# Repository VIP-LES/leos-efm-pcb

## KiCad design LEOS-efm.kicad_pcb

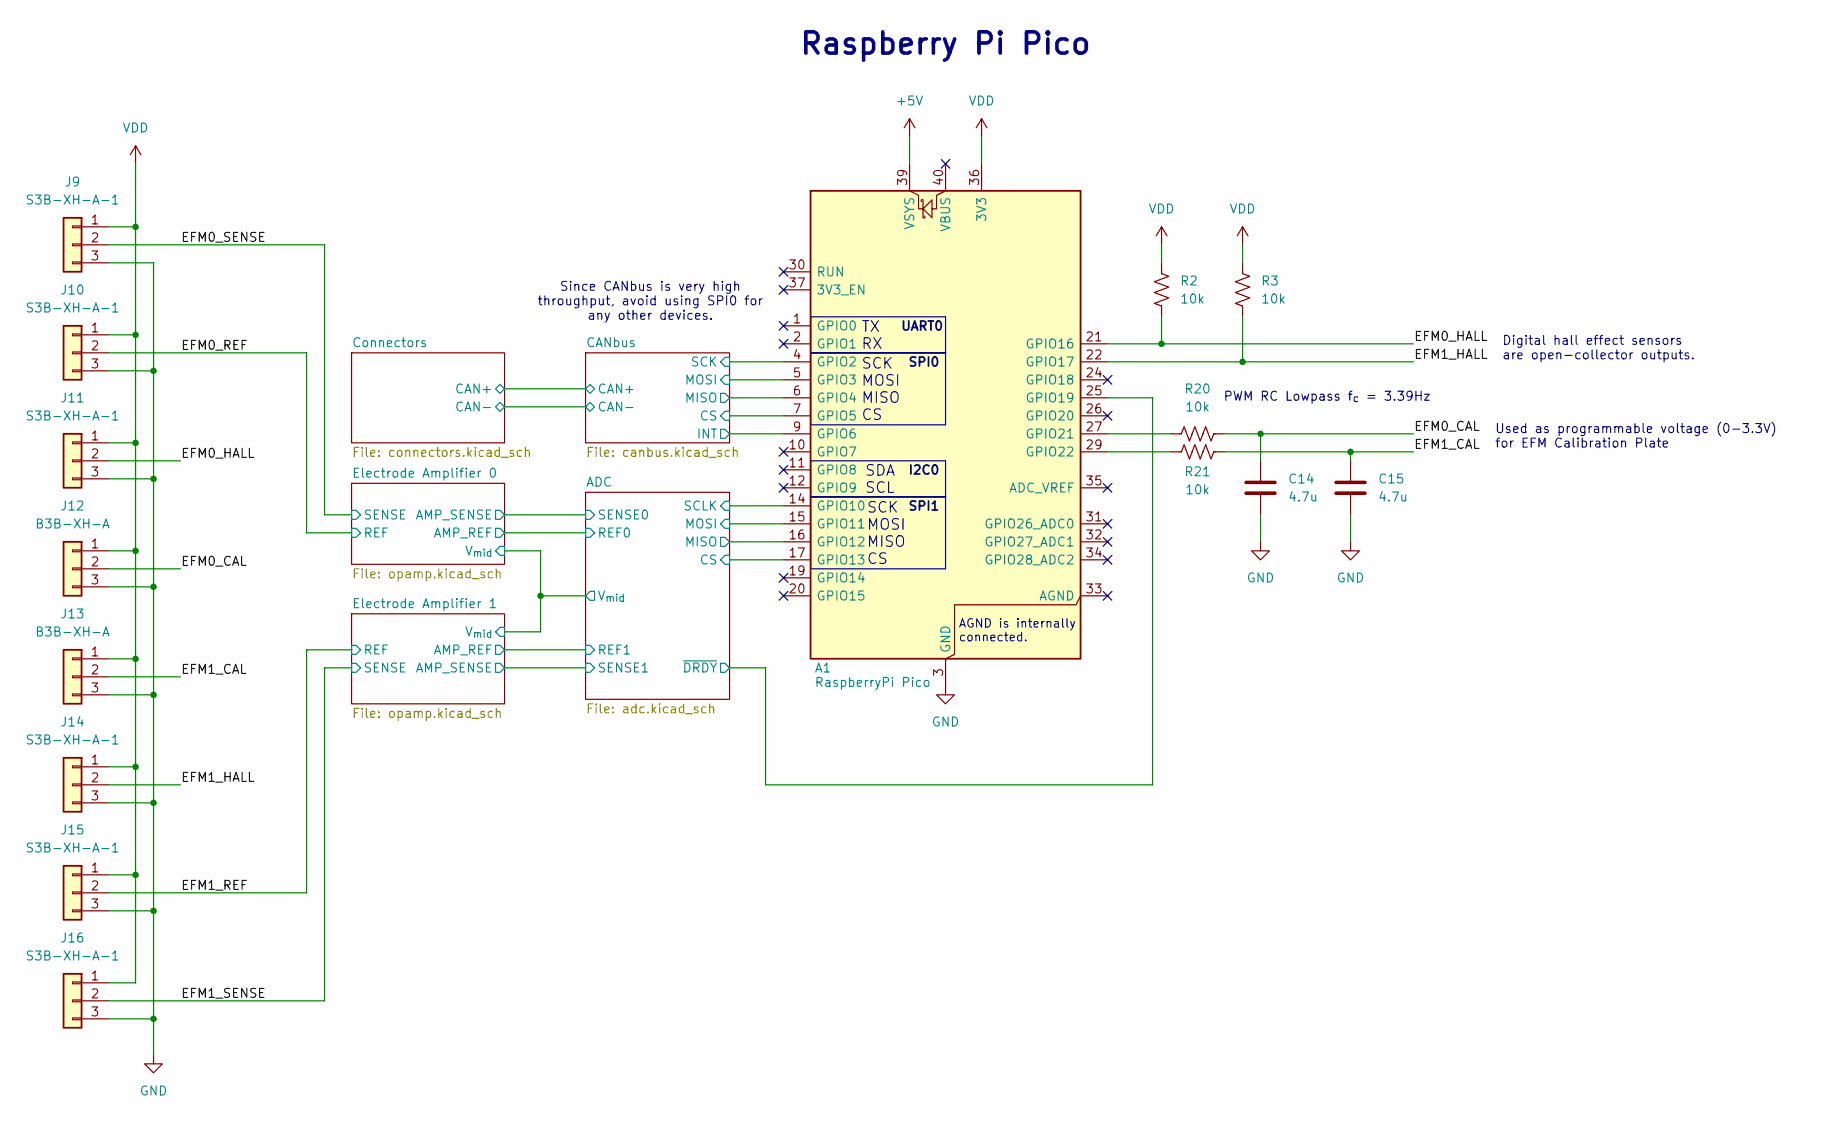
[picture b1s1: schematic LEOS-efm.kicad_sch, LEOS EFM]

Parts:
A1: RaspberryPi Pico; RaspberryPi_Pico_Common_Unspecified; MPN PIM724; Digikey 1778-PIM724-ND
C14, C15: 4.7u; C_1206_3216Metric; MPN CL31B475KBHNFNE; Digikey 1276-3179-1-ND
J9, J10, J11, J14, J15, J16: S3B-XH-A-1; JST_XH_S3B-XH-A-1_1x03_P2.50mm_Horizontal; MPN S3B-XH-A-1; Digikey 455-S3B-XH-A-1-ND
J12, J13: B3B-XH-A; JST_XH_B3B-XH-A_1x03_P2.50mm_Vertical; MPN B3B-XH-A; Digikey 455-2248-ND
R2, R3, R20, R21: 10k; R_1206_3216Metric

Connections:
+5V: A1.39 (VSYS); also elsewhere on the board
/ADC/CS: A1.17 (GPIO13); also elsewhere on the board
/ADC/MISO: A1.16 (GPIO12); also elsewhere on the board
/ADC/MOSI: A1.15 (GPIO11); also elsewhere on the board
/ADC/SCLK: A1.14 (GPIO10); also elsewhere on the board
/ADC/~DRDY: A1.25 (GPIO19); also elsewhere on the board
/CANbus/CS: A1.7 (GPIO5); also elsewhere on the board
/CANbus/INT: A1.9 (GPIO6); also elsewhere on the board
/CANbus/MISO: A1.6 (GPIO4); also elsewhere on the board
/CANbus/MOSI: A1.5 (GPIO3); also elsewhere on the board
/CANbus/SCK: A1.4 (GPIO2); also elsewhere on the board
/EFM0_CAL: C14.1, J12.2, R20.2
/EFM0_HALL: A1.21 (GPIO16), J11.2, R2.2
/EFM0_REF: J10.2; also elsewhere on the board
/EFM0_SENSE: J9.2; also elsewhere on the board
/EFM1_CAL: C15.1, J13.2, R21.2
/EFM1_HALL: A1.22 (GPIO17), J14.2, R3.2
/EFM1_REF: J15.2; also elsewhere on the board
/EFM1_SENSE: J16.2; also elsewhere on the board
GND: A1.3 (GND), A1.8 (GND), A1.13 (GND), A1.18 (GND), A1.23 (GND), A1.28 (GND), A1.38 (GND), C14.2, C15.2, J9.3, J10.3, J11.3, J12.3, J13.3, J14.3, J15.3, J16.3; also elsewhere on the board
unnamed: A1.27 (GPIO21), R20.1
unnamed: A1.29 (GPIO22), R21.1
VDD: A1.36 (3V3), J9.1, J10.1, J11.1, J12.1, J13.1, J14.1, J15.1, J16.1, R2.1, R3.1; also elsewhere on the board

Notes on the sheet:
PWM RC Lowpass f_{c} = 3.39Hz
SPI1
Raspberry Pi Pico
SCK MOSI MISO CS
Since CANbus is very high throughput, avoid using SPI0 for any other devices.
SPI0
SDA SCL
TX RX
UART0
Digital hall effect sensors are open-collector outputs.
I2C0
AGND is internally connected.
Used as programmable voltage (0-3.3V) for EFM Calibration Plate

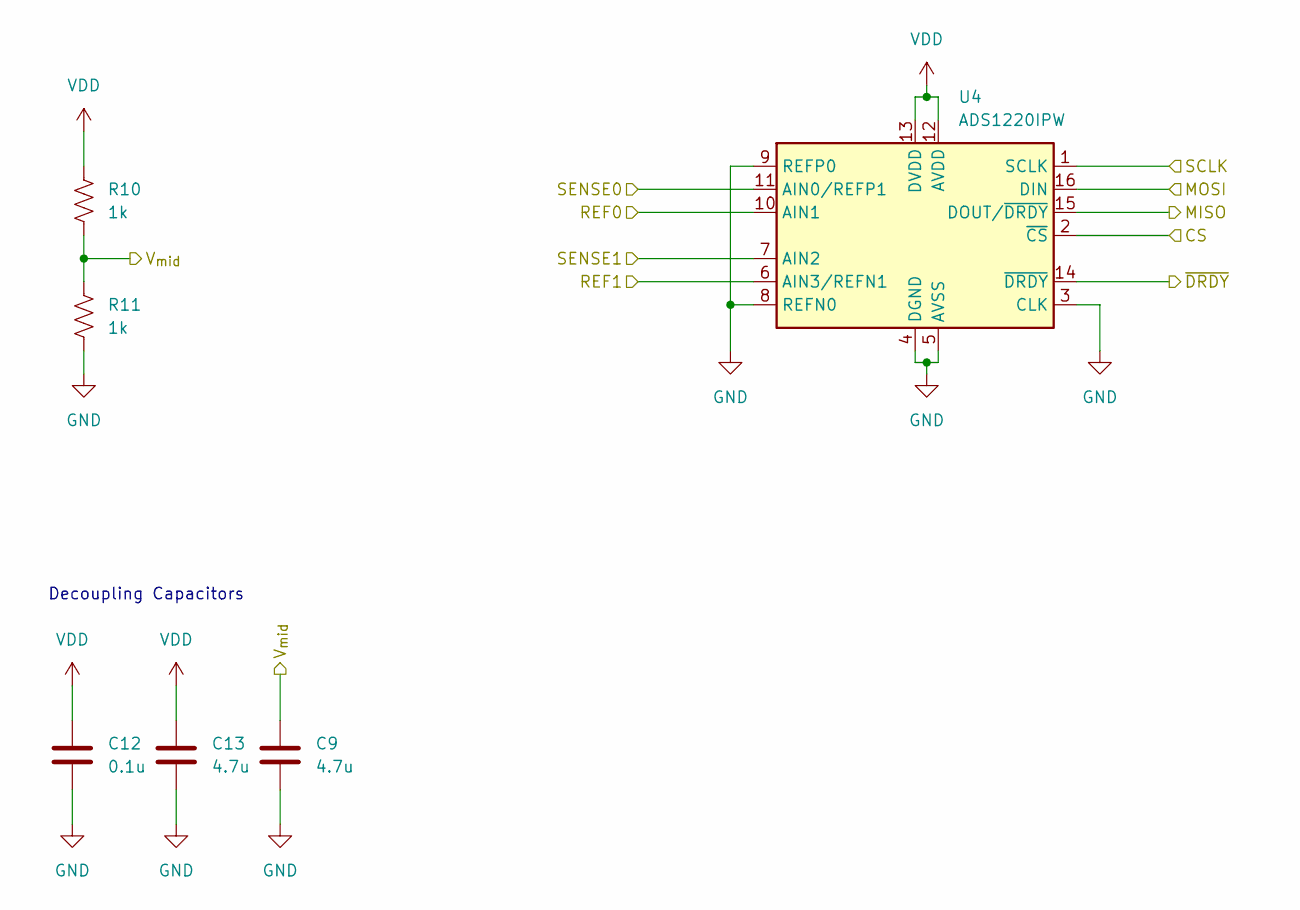
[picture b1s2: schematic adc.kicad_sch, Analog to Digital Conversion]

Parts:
C9, C13: 4.7u; C_1206_3216Metric; MPN CL31B475KBHNFNE; Digikey 1276-3179-1-ND
C12: 0.1u; C_0805_2012Metric; MPN CL21B104KBCNNNC; Digikey 1276-1003-1-ND
R10, R11: 1k; R_1206_3216Metric
U4: ADS1220IPW; TSSOP-16_4.4x5mm_P0.65mm; MPN ADS1220IPWR; Digikey 296-39851-1-ND

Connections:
/ADC/CS: U4.2 (~CS); also elsewhere on the board
/ADC/MISO: U4.15 (DOUT/~DRDY); also elsewhere on the board
/ADC/MOSI: U4.16 (DIN); also elsewhere on the board
/ADC/REF0: U4.10 (AIN1); also elsewhere on the board
/ADC/REF1: U4.6 (AIN3/REFN1); also elsewhere on the board
/ADC/SCLK: U4.1 (SCLK); also elsewhere on the board
/ADC/SENSE0: U4.11 (AIN0/REFP1); also elsewhere on the board
/ADC/SENSE1: U4.7 (AIN2); also elsewhere on the board
/ADC/V_{mid}: C9.1, R10.2, R11.1; also elsewhere on the board
/ADC/~DRDY: U4.14 (~DRDY); also elsewhere on the board
GND: C9.2, C12.2, C13.2, R11.2, U4.3 (CLK), U4.4 (DGND), U4.5 (AVSS), U4.8 (REFN0), U4.9 (REFP0); also elsewhere on the board
VDD: C12.1, C13.1, R10.1, U4.12 (AVDD), U4.13 (DVDD); also elsewhere on the board

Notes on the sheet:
Decoupling Capacitors

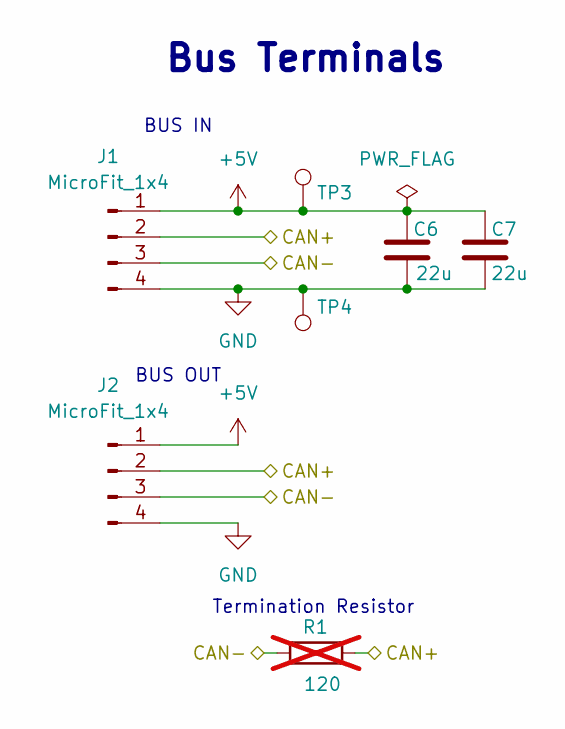
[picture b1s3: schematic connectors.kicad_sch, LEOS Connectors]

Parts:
C6, C7: 22u; C_1206_3216Metric; MPN CL31B226MPHNNNE; Digikey 1276-3148-1-ND
J1, J2: MicroFit_1x4; Molex_MicroFit3.0_43650-0410_1x04_Horizontal; MPN 0436500409; Digikey WM1882CT-ND
R1: 120; R_Axial_DIN0207_L6.3mm_D2.5mm_P7.62mm_Horizontal; MPN CF14JT120R; Digikey CF14JT120RCT-ND; not fitted
TP3: 5V Test Point; TestPoint_Loop_D2.60mm_Drill0.9mm_Beaded; MPN 5000; Digikey 36-5000-ND
TP4: GND Test Point; TestPoint_Loop_D2.60mm_Drill0.9mm_Beaded; MPN 5001; Digikey 36-5001-ND

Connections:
+5V: C6.1, C7.1, J1.1, J2.1, TP3.1 (1_1); also elsewhere on the board
/CANbus/CAN+: J1.2, J2.2, R1.2; also elsewhere on the board
/CANbus/CAN-: J1.3, J2.3, R1.1; also elsewhere on the board
GND: C6.2, C7.2, J1.4, J2.4, TP4.1 (1_1); also elsewhere on the board

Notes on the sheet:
BUS OUT
Bus Terminals
BUS IN
Termination Resistor

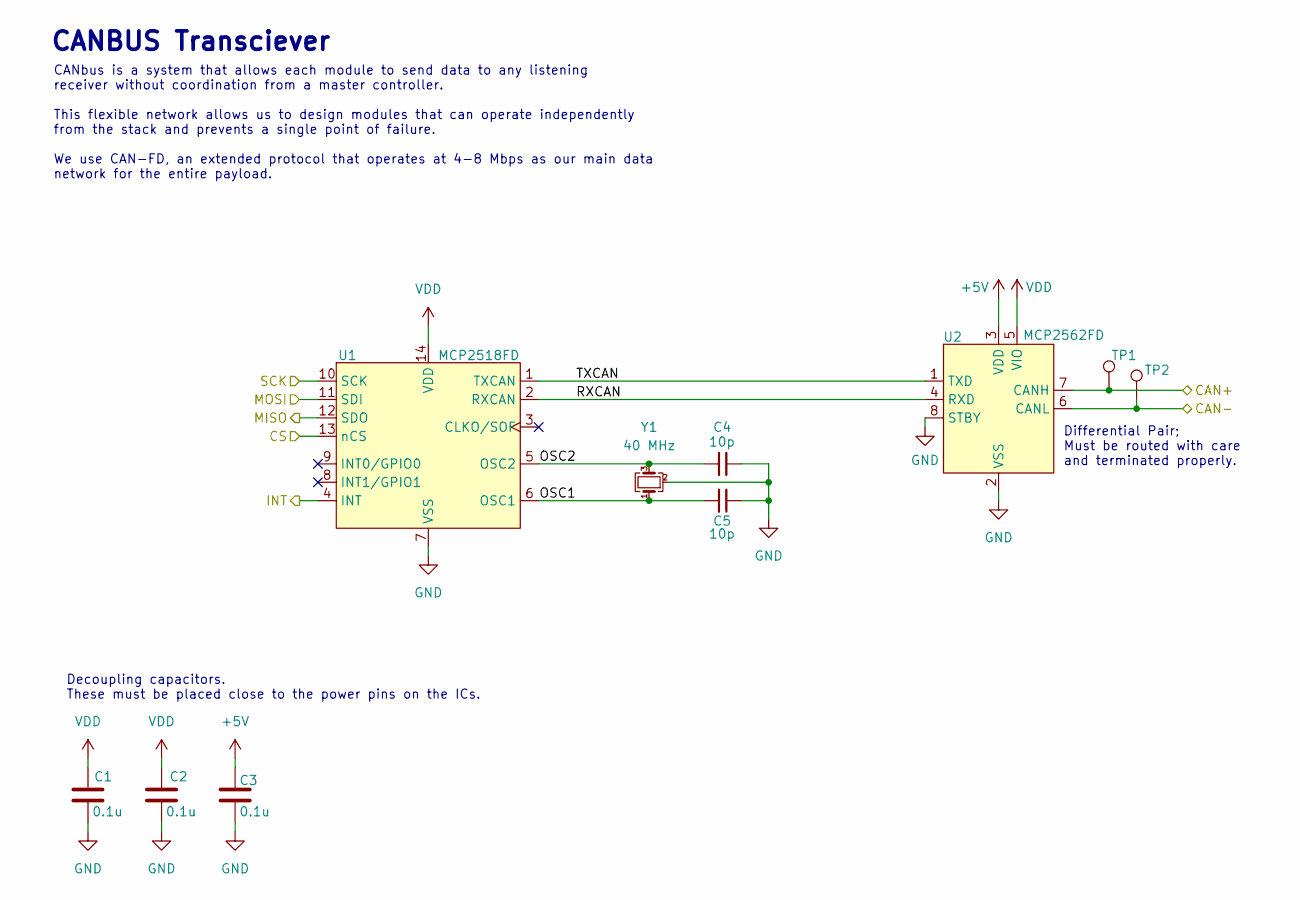
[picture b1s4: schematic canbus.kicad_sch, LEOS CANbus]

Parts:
C1, C2, C3: 0.1u; C_0805_2012Metric; MPN CL21B104KBCNNNC; Digikey 1276-1003-1-ND
C4, C5: 10p; C_0805_2012Metric; MPN CL21C100CBANNNC; Digikey 1276-2561-1-ND
TP1: CAN-H Test Point; TestPoint_Loop_D2.60mm_Drill0.9mm_Beaded; MPN 5004; Digikey 36-5004-ND
TP2: CAN-L Test Point; TestPoint_Loop_D2.60mm_Drill0.9mm_Beaded; MPN 5116; Digikey 36-5116-ND
U1: MCP2518FD; SOIC-14_3.9x8.7mm_P1.27mm; MPN MCP2518FDT-E/SL; LCSC C626758
U2: MCP2562FD; SOIC-8_3.9x4.9mm_P1.27mm; MPN MCP2562FDT-H/SN; LCSC C511335
Y1: 40 MHz; Crystal_SMD_2016-4Pin_2.0x1.6mm; MPN ECS-400-10-37B2-CKY-TR; Digikey 50-ECS-400-10-37B2-CKY-TRCT-ND

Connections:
+5V: C3.1, U2.3 (VDD); also elsewhere on the board
/CANbus/CAN+: TP1.1 (1_1), U2.7 (CANH); also elsewhere on the board
/CANbus/CAN-: TP2.1 (1_1), U2.6 (CANL); also elsewhere on the board
/CANbus/CS: U1.13 (nCS); also elsewhere on the board
/CANbus/INT: U1.4 (INT); also elsewhere on the board
/CANbus/MISO: U1.12 (SDO); also elsewhere on the board
/CANbus/MOSI: U1.11 (SDI); also elsewhere on the board
/CANbus/OSC1: C5.2, U1.6 (OSC1), Y1.1
/CANbus/OSC2: C4.2, U1.5 (OSC2), Y1.3
/CANbus/RXCAN: U1.2 (RXCAN), U2.4 (RXD)
/CANbus/SCK: U1.10 (SCK); also elsewhere on the board
/CANbus/TXCAN: U1.1 (TXCAN), U2.1 (TXD)
GND: C1.2, C2.2, C3.2, C4.1, C5.1, U1.7 (VSS), U2.2 (VSS), U2.8 (STBY), Y1.2 (G), Y1.4 (G); also elsewhere on the board
VDD: C1.1, C2.1, U1.14 (VDD), U2.5 (VIO); also elsewhere on the board

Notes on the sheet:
Differential Pair; Must be routed with care and terminated properly.
CANBUS Transciever
CANbus is a system that allows each module to send data to any listening receiver without coordination from a master controller. This flexible network allows us to design modules that can operate independently from the stack and prevents a single point of failure. We use CAN-FD, an extended protoco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
Decoupling capacitors. These must be placed close to the power pins on the ICs.

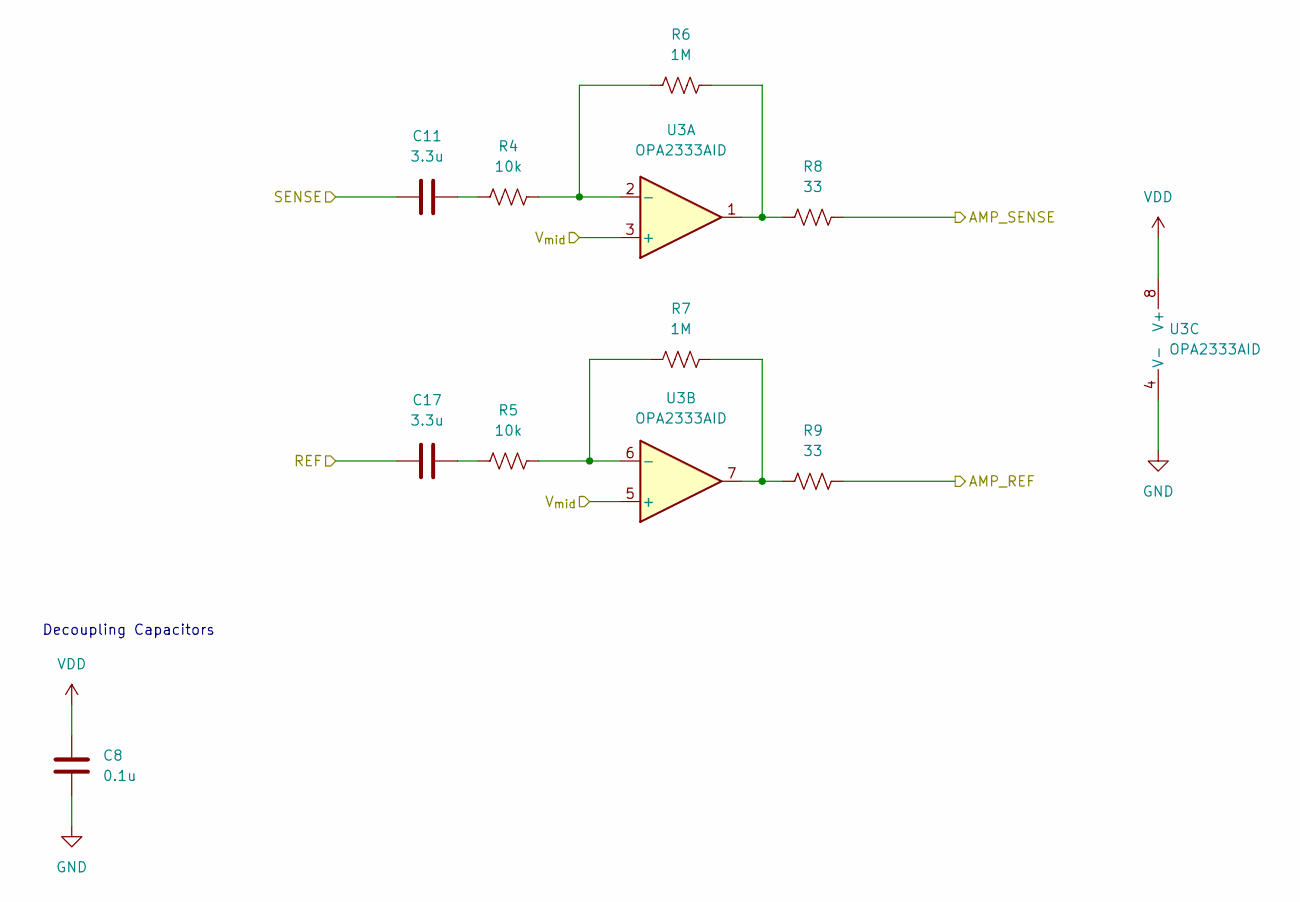
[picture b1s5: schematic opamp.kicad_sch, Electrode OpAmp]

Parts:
C8: 0.1u; C_0805_2012Metric; MPN CL21B104KBCNNNC; Digikey 1276-1003-1-ND
C11, C17: 3.3u; C_1206_3216Metric
R4, R5: 10k; R_1206_3216Metric
R6, R7: 1M; R_1206_3216Metric
R8, R9: 33; R_1206_3216Metric
U3: OPA2333AID; SOIC-8_3.9x4.9mm_P1.27mm; MPN OPA2333AID; Digikey 296-19543-5-ND

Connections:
/ADC/REF0: R9.2; also elsewhere on the board
/ADC/SENSE0: R8.2; also elsewhere on the board
/ADC/V_{mid}: U3.3 (+), U3.5 (+); also elsewhere on the board
/EFM0_REF: C17.1; also elsewhere on the board
/EFM0_SENSE: C11.1; also elsewhere on the board
GND: C8.2, U3.4 (V-); also elsewhere on the board
unnamed: C11.2, R4.1
unnamed: C17.2, R5.1
unnamed: R6.2, R8.1, U3.1
unnamed: R7.2, R9.1, U3.7
unnamed: R4.2, R6.1, U3.2 (-)
unnamed: R5.2, R7.1, U3.6 (-)
VDD: C8.1, U3.8 (V+); also elsewhere on the board

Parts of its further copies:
C10: 0.1u; C_0805_2012Metric; MPN CL21B104KBCNNNC; Digikey 1276-1003-1-ND
C16, C18: 3.3u; C_1206_3216Metric
R12, R13: 10k; R_1206_3216Metric
R14, R15: 1M; R_1206_3216Metric
R16, R17: 33; R_1206_3216Metric
U5: OPA2333AID; SOIC-8_3.9x4.9mm_P1.27mm; MPN OPA2333AID; Digikey 296-19543-5-ND

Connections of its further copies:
/ADC/REF1: R17.2; also elsewhere on the board
/ADC/SENSE1: R16.2; also elsewhere on the board
/ADC/V_{mid}: U5.3 (+), U5.5 (+); also elsewhere on the board
/EFM1_REF: C18.1; also elsewhere on the board
/EFM1_SENSE: C16.1; also elsewhere on the board
GND: C10.2, U5.4 (V-); also elsewhere on the board
unnamed: C16.2, R12.1
unnamed: C18.2, R13.1
unnamed: R14.2, R16.1, U5.1
unnamed: R15.2, R17.1, U5.7
unnamed: R12.2, R14.1, U5.2 (-)
unnamed: R13.2, R15.1, U5.6 (-)
VDD: C10.1, U5.8 (V+); also elsewhere on the board

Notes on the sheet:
Decoupling Capacitors

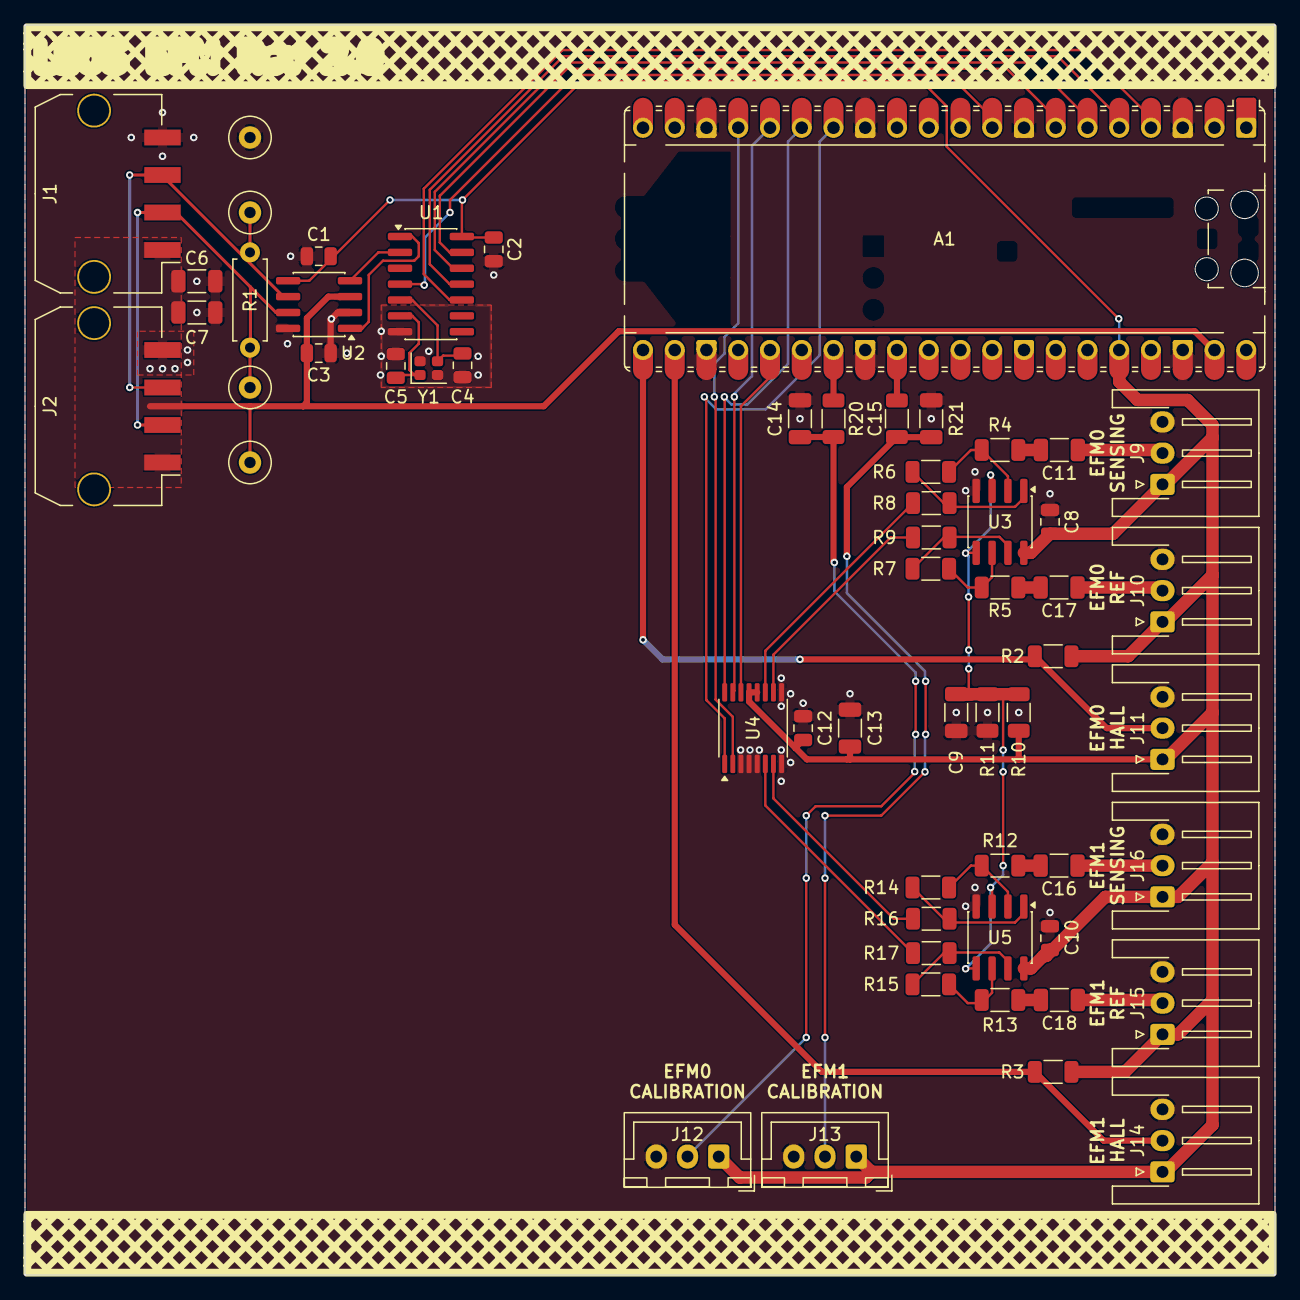
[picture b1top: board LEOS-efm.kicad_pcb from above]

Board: 2 copper layers, 100.0 x 100.0 mm, 58 parts (0 on the bottom side), 46 nets.

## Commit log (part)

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2026-02-11 Set up EFM sheet with scattered op-amps
2026-02-17 New blank
2026-02-20 v1.0
